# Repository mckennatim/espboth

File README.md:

# README EspBoth

## greenfield setup windows10 (not WSL)
1. install vscode
2. install platformio extension
can't find com port
3. install wemos driver goto https://www.wemos.cc/en/latest/ch340_driver.html. install driver with device plugged in

## resources

https://tttapa.github.io/ESP8266/Chap04%20-%20Microcontroller.html

https://steve.fi/hardware/d1-pins/

## tips
* printf doesn't always print , use Serail.println
* constant values you need access too in multiple files are best declared in a .h file ex: `struct sen_t { .... };, extern const sent_t SE;` then intialized or set in a .cpp file  ex: `const labels_t la {
  {"devtime", "cmd"},2};` 
## weird shit
* in main you have to have `Sched sched;` even though there is no use of that class in main. (req.processInc does use Sched, declaring it in Reqs is not enough) else you get

      undefined reference to `sched'
      collect2.exe: error: ld returned 1 exit status
      *** [.pio\build\d1_mini\firmware.elf] Error 1

## log

### 8/5/21 17-secstidif-CYURD200solar
new directory with different name

secstidif = Sensors-Contolled_Sensors-Timers-Differential_Controller are all the functions built into this codebase.

CYURD200solar = CYURD200 is the microcontrollers id, whose owner is tobinmckenna@gmail.com and which is running his solar project. It is also the name of the configuration file CONFUG_CYURD200solar that has been copied into CONFIG.cpp and CONFIG.h. This configuration implements 

    /*SERVER
    dev extern device variables*/
    char devid[9]="CYURD200";
    char owner[254]="tobinmckenna@gmail.com";
    char pwd[24]="xxxxx";
    char mqtt_server[60]="sitebuilt.net";
    char mqtt_port[6]="1884";
    /*dev*/

    srs_t srs {
      4,//numsr (se+cs)
      4,//numse of just sensors
      {//se:{sr,reading,rec,isnew}
        {0,45,1,0},//solar temp J9
        {1,45,1,0},//tank temp J5
        {2,45,1,0},//slab temp J4
        {3,45,1,0}//outdoor temp J8
      },
      2,//numcs
      {//cs:{sr,reading,onoff,hi,lo,isnew}
        {1,120,0,138,100,1,0}, //heatexch
        {1,121,0,180,140,1,0}  //tankles
      }, 
      0,//numti
      {},
      1,//numdi difference control
      {/*di:{sa,sb,don,doff,maxa.maxb,port,onoff,rec,isnew}
            {solar,tank, solar-tank} 
      */
        {0,1,6,2,200,200,D1,0,1,0}
      }
    };
    /*prgs extern data structure initalization*/ 
    prgs_t prgs{
      2,//numprgs
      { //prg: {sr,aid,ev,numdata,prg[[hr,min,max,min]],port,hms}
        {1,255,1,2,{{0,0,80,78}},D8,1504}, //hxch
        {1,255,1,2,{{0,0,75,71}},D7,1503}  //tankles
      }
    };

Solar  = Controller for Tobin's Solar augmented heating system which adds solar panels, a drain down tank, a storage tank and diverters to existing tankles DHW + heat exchanger feeding radiant and baseboard heat.

* copied dependencies to lib_deps in platformio.ini. Hopefully the compiler will realize what is needed and go and get them.

### 7/27/21  16-secstidef-CYURD200solar
Forget about working without wifi (for now), just make it work for these new conditions

#### 2 relays depending on 1 sensor

    { //prg: {sr,aid,ev,numdata,prg[[]],port,hms}
      {1,255,1,2,{{0,0,80,78}},D8,1504}, //hxch
      {1,255,1,2,{{0,0,75,71}},D7,1503}  //tankles
    }

No longer choosing cs idx by sr, now choosing cs by prg index

Trying to separate sensor readings and update from what happens after. You should just be able to check all your sensor values.

### 7/15/21  15-secstidef-CYURD200solar
secstidef stands for sensors, controlled sensors(like thermostats), timers and def(ault function) - the curent goal of modifying the code so it doesn't spin its wheels without the internet.

To compile copy the contents of CONFIG_CYURD200solar.cpp and .h files into CONFIG.h and CONFIG.cpp in the src directory of espBoth/secstidef/ then compile. 

I am using vscode with the platformio extension instead of the arduino gui.

To work for the solar project it needs to also work as a differential controller, ie comparing two sensors.

I put the pcb files in zKicad/esp8266v1. you would need to download kicad to mess with them

### 7/13/21 14-secstidef
At the start of Tobin's solar project.

Allow microcontroller operation in the absense of wifi. Builds on code in secsti

### 10/17/20 13-test-MAX31855zanshin
again tried to get these chips to work,
works on this 
### 4/22/20 12-secsti-CUSTON_CODE
added CUSTOM CODE
* added function declarations `void customInit(); void customLoop();` and defined the functions in CONFIG.cpp
* added calls in `main.cpp` in `initShit()` and `loop()`

Implementing Cascada

Changes to secsti needed: dr (dependant relay)

* need the funtionality that makes ouput port hi whenever any of 3 other ports are hi else lo
* has no sensor related to it or timer running with it
* has no prog

### 4/10/20 11-secsti-req_pub

### 4/9/20 10-secsti-ddd
* modified `srs` data type to distinguish between `rec` - whether you want to record new values of this sensor and `isnew` to distinguish between newly sensed values and prg settings and just requests for srstate from apps

### 4/8/20 09-espbothREADME-incoming-outgoing_message_types-INNERworkings

#### device INCOMING Message topics `/devtime/req/cmd/prg/set`

##### from server (provides data)
- [x] /devtime `{dow,unix,LLLL,zone,mysql}` -> sched.deseriTime, sched.actTime()

##### from app 

req.desiriReq()
- [x] /req `{\"id\":0, \"req\":"srstates"}`->f.HAYsTATEcNG = 31;
- [x] /req `{\"id\":1, \"req\":"sched"}` -> req.pubPrg(31)
- [x] /req `{\"id\":2, \"req\":"flags"}` ->req.pubFlags()
- [x] /req `{"id\":3, \"req\":"timr"}`  ->req.pubTimr()

req.deseriCmd() alter schedule currently running (insert into srs) 
- [x] /cmd (cs) `{"id":${sr},"sra":[hilimit,lolimit]}`
- [x] /cmd (ti) `{"id":${sr},"sra":[onoff]}`

sched.deseriProg replace program on device
uses JsonArray$ ev.size() to distinguish cs/ti
- [x] /prg (ti) `{"id":sr,"pro":[[hr,min,onoff], [7,45,0]]}`
- [x] /prg (cs) `{"id":sr,"pro":[[hr,min,hilimit,lolimit], [7,45,68,66]]}`

only now used in /spa1/aapoj/paho2&pahoRaw
- [ ] /set `{"devid":"CYURD001", "owner":"tim@sitebuilt.net", "pwd":"gekkt", "mqtt_server":"sitebuilt.net", "mqtt_port":"1884", "sensor_type":""}`

#### device OUTGOING message topics `/time/srstate/flags/timr/sched`

##### to server 
sever returns `/devtime` and `/prg` messages 
- [x] /time `the time is being requested`

##### to app 
uses `[ici.type:[se=0,cs=1.ti=2], ici.idx:idx_in_type] = req.getTypeIdx(sr);`
- [x] /srstate (se,ti) `{\"id\":sr, \"darr\":[onoff/reading], \"new\":rec}`
- [x] /srstate (cs) `{\"id\":sr, \"darr\":[reading,onoff.hilimit,lolimit], \"new\":rec}`

req.pubFlags() RUNSon req or if (f.CKaLARM>0)
- [x] /flags  `{"aUTOMA":true,"fORCErESET":false,"cREMENT":5,"HAStIMR":28,"IStIMERoN":0,"HAYpROG":0,"HAYpROGcNG":31,"HAYsTATEcNG":31,"CKaLARM":0,"ISrELAYoN":3,"tIMElEFT":[0,0,0,0,0]}`

req.pubTimr() takes everthing from flag values <br/>
RUNSon req || if (f.CKaLARM>0) || if (f.IStIMERoN >0) after sched.updTimers(); || schedAdjRelay()
- [ ] /timr `{"cREMENT":5,"IStIMERoN":0,"ISrELAYoN":3,"tIMElEFT":[0,0,0,0,0]}`

req.pubPrg(f.CKaLARM) (should be pubSched()) uses prg_t prgs, req.creaJson(), req.clPub() (not sure alarmid is needed) <br/>
RUNSon req || if (f.CKaLARM>0) 
- [x] /sched `{id:sr, aid:alarmid, ev:#ofeventsinday, numdata:cshilo/tionoff, pro:[[hr,min,onoff], [hr,min,hilimit,lolimit]] }`

#### INNER WORKINGS: f.CKaLARM
Causes the inital publication of a prg and initial publications of /timr. But more importantly it causes sched.ckAlarm() to run which set up the state to curr and sets and alarm to run until the next schedule event. After it does what it need to do in loop then clears f.CKaLARM
* in req.processIncoming /devtime it is set to 31
* if (f.CKaLARM>0) triggers req.pubPrg(f.CKaLARM) and req.pubTimr() in mail loop
* is set in sched.deseriProg on a /prg message from app or server
* sched.ckAlarms() updates prg based for (f.CKaLARM & 2) == 2)
* gets cleared (unset) in loop after it does what it causes to be done `f.CKaLARM=f.CKaLARM & 0;` sets everything to zero
* gets set in bm8() f.CKaLARM=f.CKaLARM | 8; Callback of timer resets program to next event

#### INNER WORKINGS: sched.ckAlarm() (shold be move2nextPrgEvent())
Instantiates a new program event. It runs when a new /prg message comes in or when a alarm finishes. 
* frees existing alarm and sets a new one
* changes current srs data for
  * (cs) by 
    * updating current srs (state) hilimit & lolimit from prg, 
    * sched.adjRelay() based on new cur, 
    * sets HAYsTATEcNG, 
    * sets alarmOnce() til next and gives it a callback to run when it is over
  * (ti) by 
    * updating current srs (state) onoff from prg, 
    * set f.ISrELAYoN flag if state is on
    * sched.setTleft(*p, cur, nxt, tleft); and sets f.IStIMERoN. Eventually sets f.tIMElEFT which doesn't control anything, and is just an approximation to publish to apps
    * sets alarmOnce() til next and gives it a callback to run when it is over

#### REWRITE hurdles TODO
The biggest obvious hurdle would be not to have a sched.ckAlarms with a specific callback meaning you have to hard code for each device setup or some general endless ifelse for all possible future device setups. https://forum.arduino.cc/index.php?topic=421834.0 has a possible solution. On every run through ckAlarms the alarmId can be connected to an srid. 

    struct aidsr_t {
      int:endtime; //maybe hr*600+min*10+srid
      int:sr;
      AlarmID_t aid;
    }
    struct srthm_t{
      aidsr_t aidsr[6]
    }
    
    extern srthm_t aids;

Then each time you start and alarm you can add the endtime,sr,aid to aids and then sort it https://www.youtube.com/watch?v=W4A_PxSXO1E so the next alarm that ends is on top. Then inside the cb() you can pop of the top of aids and reset f.CKaLARM for that (cs or ti).

To sort maybe I need to initalize  all the endtime to be bigger than 24*60 so that they never are on top?

?????? What if the device is scheduled to do more than one thing at a particular time? you could get the wrong srid and reschedule that srid but would you lose the other one? ANS: maybe the callback would run and the next callback will run when that one finishes. that would be good. OR ELSE DON'T SCHEDULE SR EVENTS ON A DEVICE TO RUN AT THE SAME MINUTE. Maybe that is already taken care of in ckAlarms()

    int asec = second()+id;        
    p->aid = Alarm.alarmOnce(p->prg[nxt][0],p->prg[nxt][1], asec, bm2);

### 4/7/2020 08-secsti
New codebase for esp8266 microcontrollers, should also work on esp32.

Built in `espBoth/multisensor` sensor only, no relay code. Expanded the srs data of CONFIG.h type to

        struct se_t {//sensors
          int sr;
          int reading;
          int rec;
        };
        struct cs_t {//controlled sensors
          int sr;
          int reading;
          int onoff;
          int hilimit;
          int lolimit;
          int rec;   
        };
        struct ti_t {//timers
          int sr;
          int onoff;
          int rec;   
        };
        struct srs_t {
          int numse;
          se_t se[5];
          int numcs;
          cs_t cs[1];
          int numti;
          ti_t ti[2];
        };
        extern srs_t srs;

which covers all cuurent configutation se - sensor only, cs - controlled sensor, ti - just a timer .  `main.setSrs()` distinguishes between se and cs, witing the reading to the right place and calling `sched.adjRelay()` for controlled sensors. `main.setIfDif()`  sets the sensitivity of the sensor, determining how big a change warrants publishing.   

`req.pubState()` uses `getTypeIdx(sr)` to find which srs type to read from and which local idx holds that sensors data.

### 3/29/20 07-multisensor-pubState
All sensors except max31855 working and publishing

### 3/28/20 05-multisensor-CONFIG
constant values you need access too in multiple files are best declared in a .h file ex: `struct sen_t { .... };, extern const sent_t SE;` then intialized or set in a .cpp file  ex: `const labels_t la {
  {"devtime", "cmd"},2};`

TODO - publish from the device, the current state of the sensors. PROBLEM - App is used to seeing state data from sensors with [64, 0, 68,59] even if there is no hilimit or lolimit or state.

### 3/27/20 04-multisensor-processInc_devtime
SOFAR - Added enough of `Regs.h` and `Reqs.cpp`  ans `Sched.h` and `Sched.cpp` to allow it to process incoming devtime request and set the device. THIS IS WHERE `ArduinoJson` starts to get used but left it at version 5.14.0.

Incorporated a couple of Sched member functions to respond to the handleCallback function that mqtt uses when something comes in. When something does come in the raw data is put into itopic and ipayload and then the NEW_MAIL flag is set. The main loop picks up the flag and processesIn(oming) message wheter it be {"devtime", "cmd", "prg", "req", "set", "progs"} and sched.actTime()case 0 is devtime which calls sched.deseriTime() 

weird shit: 

### 3/25/20 03-multisensor-MAX31855
SOFAR - Cannot get MAX31855 to work as sensor. Probably problem with the board

DOES NOT WORK

The SPI Interface uses 4 lines for data exchange:

* SCLK-Serial Clock: Clock signal (from lead) Ot
her designations: SCK, CLK
* MOSI-Master Output, Slave Input: Data from leading to Vedomo
mudrugie notation: SDI, DI, SI
* MISO — Master Input, Slave Output: Data from the Vedushhemudrug
ie-driven notation: SDO, do, SO
* SS-Slave Select: Slave selection; is established by the
Other designations: nCS, CS, CSB, CSN, nSS, STE

MAX 31855 still not working  (probably board problem not SPI) though Nokia 5110 SPI display does (in test)

* CLK - > D5(14)SCK
* CS  ->  D8(15)SS
* D0  ->  D6(12)MISO
### 3/24/20 02-multisensor-mq
SOFAR - Moved light code to multsensors and added some sensors as well as `MQclient.h` and `MQclient.cpp` and added db entries so the device could connect to the mqtt broker. `MQclient.cpp` makes a proper request to the broker for the proper time and the broker hears it.

* CONST.h to set up a device. trying to allow processing of input by stepping through arrays
* Leaving build flags D in platfromio.ini
* mq works but maybe should not be sticking with ArduinoJSON 5.13 as I move on
* sensors working so far 
    * BH1750 light sensor. Light sensor id sn i2c device. 
    * DS18B20 onewire temp sensor. Can have multiple banks of multiple sensors
    * DHT11/22 remember dht.begin()
    * hygrometer uses analog A0 constrain and map

### 3/21/20 00-light+config
SOFAR - Added `config.h` and `config.c` to run the code to connect to WIFI

### 3/20/20 00-light
SOFAR - just sensors working without internet using a new `CONST.h` as a config file, now being able to iterate through it in `redSensors()`

^REBUILDING THE CODEBASE^

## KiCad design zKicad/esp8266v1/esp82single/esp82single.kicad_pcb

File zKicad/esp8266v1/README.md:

https://jlcpcb.com/client/index.html#/order

https://randomnerdtutorials.com/esp8266-multisensor-shield/

https://hackaday.com/2018/09/07/create-your-own-esp8266-shields/

for freerouting export as session .dsn file. Open FreeRouting.jar from the decktop, wait, autoroute, and export as session file

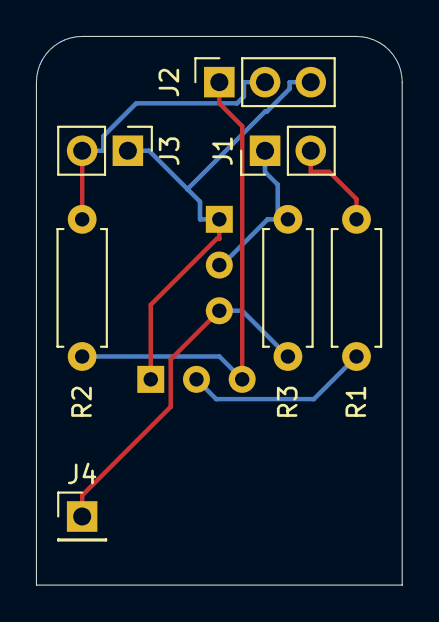
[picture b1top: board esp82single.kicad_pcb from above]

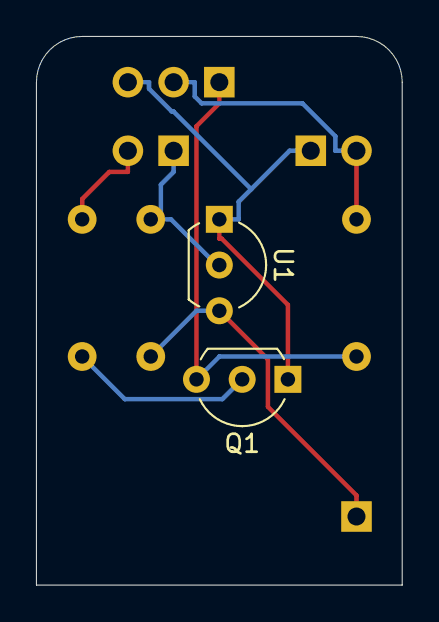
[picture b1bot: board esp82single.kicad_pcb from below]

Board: 2 copper layers, 20.3 x 30.5 mm, 9 parts (2 on the bottom side), 7 nets.

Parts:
J1: in_out; PinHeader_1x02_P2.54mm_Vertical
J2: cat5; PinSocket_1x03_P2.54mm_Vertical
J3: 5v_G; PinHeader_1x02_P2.54mm_Vertical
J4: 3.3v; PinHeader_1x01_P2.54mm_Vertical
Q1: 2N2222A; TO-92L_Inline_Wide
R1: 1k; R_Axial_DIN0207_L6.3mm_D2.5mm_P7.62mm_Horizontal
R2: 470; R_Axial_DIN0207_L6.3mm_D2.5mm_P7.62mm_Horizontal
R3: 4.7k; R_Axial_DIN0207_L6.3mm_D2.5mm_P7.62mm_Horizontal
U1: DS18B20; TO-92L_Inline_Wide

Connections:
+3V3: J4.1, R3.1, U1.3
+5V: J2.2, J3.2, R2.1
GND: J2.3, J3.1, Q1.1, U1.1
unnamed: J1.1, R3.2, U1.2
unnamed: J1.2, R1.2
unnamed: J2.1, Q1.3, R2.2
unnamed: Q1.2, R1.1

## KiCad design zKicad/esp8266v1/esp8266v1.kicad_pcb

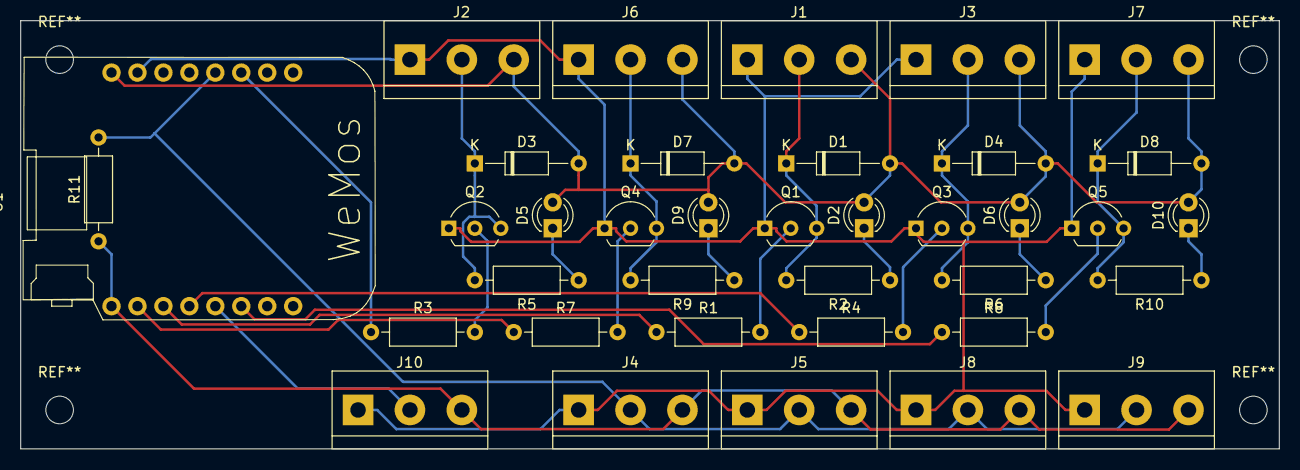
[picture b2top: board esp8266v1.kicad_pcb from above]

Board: 2 copper layers, 123.2 x 41.9 mm, 37 parts (0 on the bottom side), 25 nets.

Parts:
D1, D3, D4, D7, D8: DIODE; D_DO-35_SOD27_P10.16mm_Horizontal
D2, D5, D6, D9, D10: LED; LED_D3.0mm_Clear
J1: Out3; TerminalBlock_bornier-3_P5.08mm
J2: Out1; TerminalBlock_bornier-3_P5.08mm
J3: Out4; TerminalBlock_bornier-3_P5.08mm
J4: Inp1; TerminalBlock_bornier-3_P5.08mm
J5: Inp2; TerminalBlock_bornier-3_P5.08mm
J6: Out2; TerminalBlock_bornier-3_P5.08mm
J7: Out5; TerminalBlock_bornier-3_P5.08mm
J8: Inp3; TerminalBlock_bornier-3_P5.08mm
J9: Inp4; TerminalBlock_bornier-3_P5.08mm
J10: Inp0; TerminalBlock_bornier-3_P5.08mm
Q1, Q2, Q3, Q4, Q5: 2N2219; TO-92L_Inline_Wide
R1, R3, R4, R7, R8: 1k; R_Axial_DIN0207_L6.3mm_D2.5mm_P10.16mm_Horizontal
R2, R5, R6, R9, R10: 150; R_Axial_DIN0207_L6.3mm_D2.5mm_P10.16mm_Horizontal
R11: 47k; R_Axial_DIN0207_L6.3mm_D2.5mm_P10.16mm_Horizontal
U1: WeMos_mini; D1_mini_board

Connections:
+3V3: J4.3, J5.3, J8.3, J9.3, J10.3, R11.1, U1.16
+5V: D1.2, D2.2, D3.2, D4.2, D5.2, D6.2, D7.2, D8.2, D9.2, D10.2, J1.3, J2.3, J3.3, J6.3, J7.3, U1.1
/inD2ds18b20: J4.2, J5.2, J8.2, J9.2, R11.2, U1.5
/inD5dht: J10.2, U1.12
/outD0temp2: R8.1, U1.11
/outD1temp1: R3.1, U1.6
/outD6timr3: R4.1, U1.13
/outD7timr2: R1.1, U1.14
/outD8timr1: R7.1, U1.15
GND: J1.1, J2.1, J3.1, J4.1, J5.1, J6.1, J7.1, J8.1, J9.1, J10.1, Q1.1, Q2.1, Q3.1, Q4.1, Q5.1, U1.2
unnamed: D1.1, J1.2, Q1.3, R2.2
unnamed: D2.1, R2.1
unnamed: D3.1, J2.2, Q2.3, R5.2
unnamed: D4.1, J3.2, Q3.3, R6.2
unnamed: D5.1, R5.1
unnamed: D6.1, R6.1
unnamed: D7.1, J6.2, Q4.3, R9.2
unnamed: D8.1, J7.2, Q5.3, R10.2
unnamed: D9.1, R9.1
unnamed: D10.1, R10.1
unnamed: Q1.2, R1.2
unnamed: Q2.2, R3.2
unnamed: Q3.2, R4.2
unnamed: Q4.2, R7.2
unnamed: Q5.2, R8.2

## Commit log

2021-07-13 14-secstidef
2021-07-19 15-secstidef-CYURD200solar
2021-07-27 16-secstidef-CYURD200solar
2021-08-05 17-secstidif-CYURD200solar
2021-10-05 nohaywifi
